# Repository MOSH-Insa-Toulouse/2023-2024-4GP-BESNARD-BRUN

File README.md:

# 2023-2024 : Capteur low-tech Graphite (Niels Brun &amp; Paul Besnard)

## SOMMAIRE
*** 
  - [Contexte](#contexte)
  - [Livrables](#livrables)
  - [Matériel nécessaire](#matériel-nécessaire)
  - [1. Simulation électronique du capteur sous LTSpice](#simulation-électronique-du-capteur-sous-ltspice)
  - [2. Design du PCB sous KiCad](#design-du-pcb-sous-kicad)
  - [3. Code arduino](#code-arduino)
  - [4. Application android APK sous MIT App Inventor](#application-android-apk-sous-mit-app-inventor)
  - [5. Réalisation du shield](#réalisation-du-shield)
  - [6. Banc de test](#banc-de-test)
  - [7. Datasheet](#datasheet)
  - [Contact](#contact) 

*** 

## Contexte
&nbsp;&nbsp;&nbsp;&nbsp;&nbsp;&nbsp;Dans le cadre de l'UF "Du capteur au banc de test" se déroulant en 4ème année de Génie Physique de l’INSA Toulouse, nous avons développé un dispositif permettant de mesurer la contrainte. Le capteur du dispositif est basé sur l'article "Pencil Drawn Strain Gauges and Chemiresistors on Paper" (Cheng-Wei Lin*, Zhibo Zhao*, Jaemyung Kim & Jiaxing Huang). Il est simplement composé d'un bout de papier avec du graphite que l'on vient déposer à l'aide d'un crayon à papier. En déformant le papier, le nombre de particules de graphite reliées, composant le crayon à papier déposé sur le papier, varie en fonction du type de déformation. Ce système granulaire subit une modification de résistance et de conductance. Grâce à cela, on  pourra remonter à la déformation tel une jauge de contrainte traditionnel. \
&nbsp;&nbsp;&nbsp;&nbsp;&nbsp;&nbsp;L'objectif est donc de pouvoir réaliser un dispositif permettant la mesure de déformation à partir d'un capteur low-tech. En passant par différentes étapes : simulations électroniques, design du PCB, code arduino et réalisation de datasheet.

## Livrables
- Un Shield PCB relié à une carte arduino UNO avec différents composants : un capteur graphite, un amplificateur transimpédance et un module bluetooth. Il peut également avoir un écran OLED, un flex sensor commercial, un potentiomètre digital, encodeur rotatoire ou des boutons.
- Un code arduino qui gère les différents composants cités précédemments (mesures de contraintes, échanges bluetooth et OLED, potentiomètre digital et boutons)
- Une application Android (sous MIT App Inventor) interfaçant le PCB et le code arduino.
- Un code arduino réalisant les essais de banc de test sur les mesures de contraintes.
- Une datasheet sur le capteur de contrainte.

&nbsp;&nbsp;&nbsp;&nbsp;&nbsp;&nbsp;Nous avons opté pour l'ajout d'un écran OLED, du flex sensor commercial, du potentiomètre digital. Egalement, nous avons choisi l'implémentation de 3 boutons plutôt que de l'encodeur rotatoire.

## Matériel nécessaire
Pour réaliser notre dispositif électronique, voici la liste des composants nécessaires :

- Résistances : 1 de 1 $k\ohm$, 1 de $10k\ohm$, 2 de $100k\ohm$ pour l'amplificateur transimpédance. 3 de $10k\ohm$ pour les boutons (peuvent être éviter en utilisant les résistances internes de l'arduino) et 1 de $47k\ohm$ pour le flex sensor.
- Capacités : 3 de 100 nF, 1 de 1 uF
- Arduino Uno
- Amplificateur opérationnel LTC1050
- Potentiomètre digital MCP41050
- Module Bluetooth HC05
- Ecran OLED 128x64
- Flex Sensor
- 3 boutons

## Simulation électronique du capteur sous LTSpice
&nbsp;&nbsp;&nbsp;&nbsp;&nbsp;&nbsp;Notre capteur de graphite possède une résistance variable de l'ordre du gigaohm. Le courant alors généré lorsque l'on applique une tension de 5V aux bornes du capteur est très faible (de l'ordre de la dizaine de nanoampères). Ainsi, pour récupérer et pouvoir analyser ce signal, nous devons l'amplifier. C'est pourquoi nous avons utilisé un montage transimpédance constitué d'un amplificateur opérationnel (AOP) pour fournir un signal en tension suffisant au convertisseur analogique-numérique (ADC) d'une carte Arduino UNO. \
Nous avons testé ce montage sur le logiciel LTspice basé sur [ce schéma](https://github.com/MOSH-Insa-Toulouse/2023-2024-4GP-BESNARD-BRUN/blob/main/Images/LTspice/schema_suggere.png) . Voici son schéma :

&nbsp;&nbsp;&nbsp;&nbsp;&nbsp;&nbsp;Concernant le choix de notre AOP, celui-ci devait être capable d'accepter en entrée un très faible courant. Il doit également avoir un offset de tension très faible afin de ne pas fausser les valeurs de tension transmises à l'ADC qui seront ensuite analysées. C'est pourquoi nous avons choisi le LTC 1050.
A ce circuit amplificateur, nous avons ajouté trois filtres pour notre signal :

- à l'entrée, un filtre passe-bas passif (R1,C1) de fréquence de coupure de 16 Hz. Il permet de filtrer les bruits en courant sur le signal d'entrée
- un autre filtre passe bas de fréquence de coupure de 1.6 Hz (R3,C4) couplé à l'AOP. Ce filtre actif permet de filtrer la composante du bruit à 50 Hz provenant du réseau électrique
- à la sortie de l'amplificateur, un dernier filtre (R6,C2) de 1.6 kHz permet de retirer le bruit créé en cours de traitement (bruits des alimentation, de l'horloge etc...)

&nbsp;&nbsp;&nbsp;&nbsp;&nbsp;&nbsp;Egalement, nous avons placé la capacité C3 de sorte à ce qu'elle filtre le bruit de l'alimentation. Aussi, la résistance R5 en entrée protège l'AOP contre les décharges électrostatiques en plus de formé avec la capacité C1 un filtre pour les bruits en tension. Enfin, la résistance R2 sera remplacé plus tard par un potentiomètre digital. Cela nous permettra de régler le gain de notre AOP en fonction de nos besoins.

Nous avons donc testé notre circuit afin de savoir si nos filtres seraient efficients :

Voici la réponse de notre circuit pour vérfier que le capteur soit correctement amplifié : 

Le signal est amplifié à 1V donc l'arduino UNO pourra le mesurer.

Enfin, voici la réponse lorsque l'on simule un courant alternatif pour vérifier que le bruit est bien filtré.

On remarque que le bruit est bien atténué, à 50Hz, il est atténue d'environ 72 dB.

## Design du PCB sous KiCad

&nbsp;&nbsp;&nbsp;&nbsp;&nbsp;&nbsp;Afin de réaliser notre PCB, nous avons reproduit le circuit précédent sur Kicad 7.0. 
Nous avons remplacé la résistance R2 par un potentiomètre numérique afin de pouvoir faire varier le gain de notre AOP. Egalement, nous avons rajouté divers composants afin de pouvoir mesurer efficacement notre capteur graphite et comparé les résultats obtenus :
- un flexsensor servant de témoin, afin de pouvoir comparer nos mesures avec celle du capteur en graphite
- un module bluetooth HC-05 afin de pouvoir communiquer avec notre circuit depuis notre téléphone depuis une application mobile que nous coderons nous-même. 
- un écran OLED ainsi que trois boutons poussoirs afin de pouvoir visualiser le résultats de nos mesures et pouvoir naviguer simplement dans les différents menus permettant diverses mesures

&nbsp;&nbsp;&nbsp;&nbsp;&nbsp;&nbsp;Tous nos composants seront installés sur un shield d'Arduino UNO. 

&nbsp;&nbsp;&nbsp;&nbsp;&nbsp;&nbsp;Nous avons commencé par réaliser les symboles des différents composants et reproduire le schéma électrique complet sur Kicad. Voici le schéma électrique de l'ensemble de notre montage :

&nbsp;&nbsp;&nbsp;&nbsp;&nbsp;&nbsp;Nous avons par la suite réalisé les empreintes de nos composants afin de les placer sur notre PCB. Notre difficulté principale a été de placer les composants de sorte qu'il n'y ait pas de via, notamment pour le GND. Voici le résultat final :

&nbsp;&nbsp;&nbsp;&nbsp;&nbsp;&nbsp;Et voici le rendu 3D que nous obtenu avec ces routages : 

&nbsp;&nbsp;&nbsp;&nbsp;&nbsp;&nbsp;Toutes les ressources utilisées pour notre Kicad (empreintes, schéma etc...) sont disponibles dans notre [dossier Kicad](https://github.com/MOSH-Insa-Toulouse/2023-2024-4GP-BESNARD-BRUN/tree/main/Kicad).

## Code arduino
&nbsp;&nbsp;&nbsp;&nbsp;&nbsp;&nbsp;Nous avons utilisé l'IDE Arduino 2.3.2. Nous avons utilisé les librairies SoftwareSerial pour le bluetooth et Adafruit_SSD1306 pour l'écran OLED. Sur cette dernière, elle utilise beaucoup de RAM pour les buffers, cette utilisation de RAM n'est pas affiché par l'IDE Arduino. Il se peut que le programme ne se lance pas si une attention n'a pas été porté sur cette utilisation de RAM. Pour éviter cela, on peut utiliser  la fonction ["F()"](https://www.arduino.cc/reference/en/language/variables/utilities/progmem/), utiliser des librairies pour l'écran OLED moins gourmandes ou enfin diminuer la résolution de l'écran.

&nbsp;&nbsp;&nbsp;&nbsp;&nbsp;&nbsp;Dans le [dossier arduino](https://github.com/MOSH-Insa-Toulouse/2023-2024-4GP-BESNARD-BRUN/tree/main/Arduino) se trouve les différents fichiers pour tester les multiples éléments du dispositif. \
Concernant le [fichier principal](https://github.com/MOSH-Insa-Toulouse/2023-2024-4GP-BESNARD-BRUN/blob/main/Arduino/Main/Main.ino) : lors de la mise sous tension de l'arduino, une première calibration du potentiomètre digitale est faite en fonction de la valeur mesurée sur le capteur graphite. 
Suite à cela, le dispositif est par défaut dans le menu déroulant avec 4 choix : 
- une mesure instantannée toutes les 500 ms
- une mesure moyennée sur 2500 ms
- une mesure du flex sensor commercial et enfin 
- une calibration du potentiomètre digital

&nbsp;&nbsp;&nbsp;&nbsp;&nbsp;&nbsp;Le choix de menu se fait grâce aux 3 boutons : un pour descendre dans le menu, un pour monter dans le menu et un troisième pour valider le choix. Ce dernier bouton de validation sert également à sortir du menu choisi.

&nbsp;&nbsp;&nbsp;&nbsp;&nbsp;&nbsp;Chaque choix du menu appel une fonction différente qui réalise sa mesure et qui est envoyé à la fonction DisplayAndTransmitter afin de l'afficher sur l'écran OLED et l'envoyer sur l'application bluetooth. Tant que le bouton central de "validation" n'est pas appuyé, on reste dans cette boucle de mesure et d'affichage.

&nbsp;&nbsp;&nbsp;&nbsp;&nbsp;&nbsp;Le calcul de la résistance du capteur en graphite se fait avec : $$Res=R1*(1+\frac{R3}{R2})*\frac{Vcc}{Vadc}-R1-R5$$ \
&nbsp;&nbsp;&nbsp;&nbsp;&nbsp;&nbsp;Et dans notre cas, notre résistance R2 est variable : c'est celle du potentiomètre digital qui est calculé avec : $`R2=\frac{47500*pos}{256}+125`$ où notre $47500$ correspond à la valeur de résistance maximale de notre MCP41050 et $pos$ la position du potentiomètre parmi les 256 valeurs.

## Application android APK sous MIT App Inventor
&nbsp;&nbsp;&nbsp;&nbsp;&nbsp;&nbsp;Une application est également disponible avec le dispositif : développé sous [MIT App Inventor](https://appinventor.mit.edu/) . 

&nbsp;&nbsp;&nbsp;&nbsp;&nbsp;&nbsp;L'application reçoit les données transmis par le module bluetooth HC-05. Elle affiche ensuite la valeur tranmis (des $M\ohm$ pour le capteur graphite ou des $\ohm$ pour le flex sensor.

&nbsp;&nbsp;&nbsp;&nbsp;&nbsp;&nbsp;L'application peut s'installer [sous android ici](https://github.com/MOSH-Insa-Toulouse/2023-2024-4GP-BESNARD-BRUN/tree/main/Android/CapteurGraphite.apk) et toutes les informations liées à l'application son dans [le dossier Application Android](https://github.com/MOSH-Insa-Toulouse/2023-2024-4GP-BESNARD-BRUN/tree/main/Android)

## Réalisation du shield

&nbsp;&nbsp;&nbsp;&nbsp;&nbsp;&nbsp;Grâce à notre Kicad, nous avons pu éditer un masque de gravure de notre PCB. Nous avons envoyé notre projet Kicad à Cathy qui s'est chargée de l'imprimer. Elle a ensuite insolé aux UV une plaque d'Epoxy recouverte d'une fine couche de cuivre et d'une résine photosensible. Puis, elle a plongé la plaquette insolée dans du révélateur afin de retirer la résine non insolée, puis dans du perchlorure de fer afin de graver les pistes. Enfin, elle a nettoyé notre plaquette avec de l'acétone afin de retirer la résine restante. Merci beaucoup à Cathy qui a pris le temps de tirer notre PCB et nous expliquer le processus de fabrication!

&nbsp;&nbsp;&nbsp;&nbsp;&nbsp;&nbsp;Nous avons ensuite procéder au perçage de notre plaquette afin de pouvoir installer nos différents composants selon le schéma du PCB obtenu grâce à Kicad. Une fois le perçage terminé, nous avons soudé nos composants à la plaquette.

&nbsp;&nbsp;&nbsp;&nbsp;&nbsp;&nbsp;Lors de cette étape, l'installation de nos composants a été plus compliquée que prévue. En effet, l'ensemble de nos trous étaient légèrement décalés par rapport à leur emplacement prévu. L'origine de ce problème n'a pas été clairement établie.

## Banc de test

&nbsp;&nbsp;&nbsp;&nbsp;&nbsp;&nbsp;Pour spécifier notre capteur et son montage transimpédance, nous avons décidé d'utiliser des demis-cercles avec un rayon différents.

&nbsp;&nbsp;&nbsp;&nbsp;&nbsp;&nbsp;Ce sont des demis-cercles, imprimés en 3D, avec un diamètre commençant à 2 cm pour le plus petit et en augmentant de 0.5 cm par créneau. Le plus grand demi-cercle a un diamètre de 5cm. Grâce à ces demis-cercles, nous allons pouvoir calculer la variation de la résistance électrique $\frac{\Delta R}{R_0}$ en fonction de la déformation $\epsilon=\frac{e}{D}$. Nous avons ici mesuré notre épaisseur de notre papier $e=0.2 mm$. Ainsi, nous avons une déformation variant de 0.1 pour le plus petit diamètre à 0.04 pour le plus grand. Voici les courbes caractéristiques pour des crayons 2B, B et HB pour [des tensions ou des compressions.](https://github.com/MOSH-Insa-Toulouse/2023-2024-4GP-BESNARD-BRUN/tree/main/Images/Compression-Tension.png)

&nbsp;&nbsp;&nbsp;&nbsp;&nbsp;&nbsp;On remarque que la résistance augmente lorsque l'on met le capteur en tension et qu'elle diminue lors de la compression de ce dernier. En tension, la distance entre les atomes de carbones augmente et la résistance augmente avec. Le contraire se produit pour la compression. \
&nbsp;&nbsp;&nbsp;&nbsp;&nbsp;&nbsp;En fonction de la dureté du crayon utilisé, les variations relatives de résistance changent. Plus le crayon est gras (2H->H->HB->B->2B avec 2B avec le plus de carbone), moins sa variation relative de résistance est élevée.

&nbsp;&nbsp;&nbsp;&nbsp;&nbsp;&nbsp;De plus, contrairement, à l'article "Pencil Drawn Strain Gauges and Chemiresistors on Paper" (Cheng-Wei Lin*, Zhibo Zhao*, Jaemyung Kim & Jiaxing Huang), nous avons pu mesurer la résistance avec un crayon 2H.

&nbsp;&nbsp;&nbsp;&nbsp;&nbsp;&nbsp;Enfin, on peut comparer notre capteur avec un flex sensor commercial. Il semblerait que le flex sensor soit plus sensible à la déformation, en plus d'être plus solide pour des déformations importantes. Pour notre capteur, il a un nombre d'utilisation très limité, qui diminue très fortement pour une déformation élevée.

&nbsp;&nbsp;&nbsp;&nbsp;&nbsp;&nbsp;Néanmoins, toutes ces mesures sont à prendre avec du recul au vu des conditions non reproductibles d'essai. En effet, la quantité de graphite déposée au crayon à papier est très variable, induisant ainsi une résistance très variable. Il serait intéressant de développer une méthode afin de déposer une quantité fixe et reproductible de graphite.
&nbsp;&nbsp;&nbsp;&nbsp;&nbsp;&nbsp;Egalement, nous conseillerons de changer de banc de test et d'utiliser un servo-moteur qui permet de créer des conditions plus reproductibles, que ce soit pour le carbone qui n'est pas déposé sur le banc de test mais également par l'angle imposé qui est précisement connu. Autrement, il faudrait reproduire des cercles de diamètres connues mais avec des déformations moins importantes afin de moins endommager le capteur.

## Datasheet

&nbsp;&nbsp;&nbsp;&nbsp;&nbsp;&nbsp; Vous pouvez retrouver la datasheet du produit [ici](https://github.com/MOSH-Insa-Toulouse/2023-2024-4GP-BESNARD-BRUN/tree/main/datasheet.pdf)

## Contact

&nbsp;&nbsp;&nbsp;&nbsp;&nbsp;&nbsp;Vous pouvez nous contacter pour toutes questions :
- Niels Brun : niels.brun@insa-toulouse.fr
- Paul Besnard : paul.besnard@insa-toulouse.fr

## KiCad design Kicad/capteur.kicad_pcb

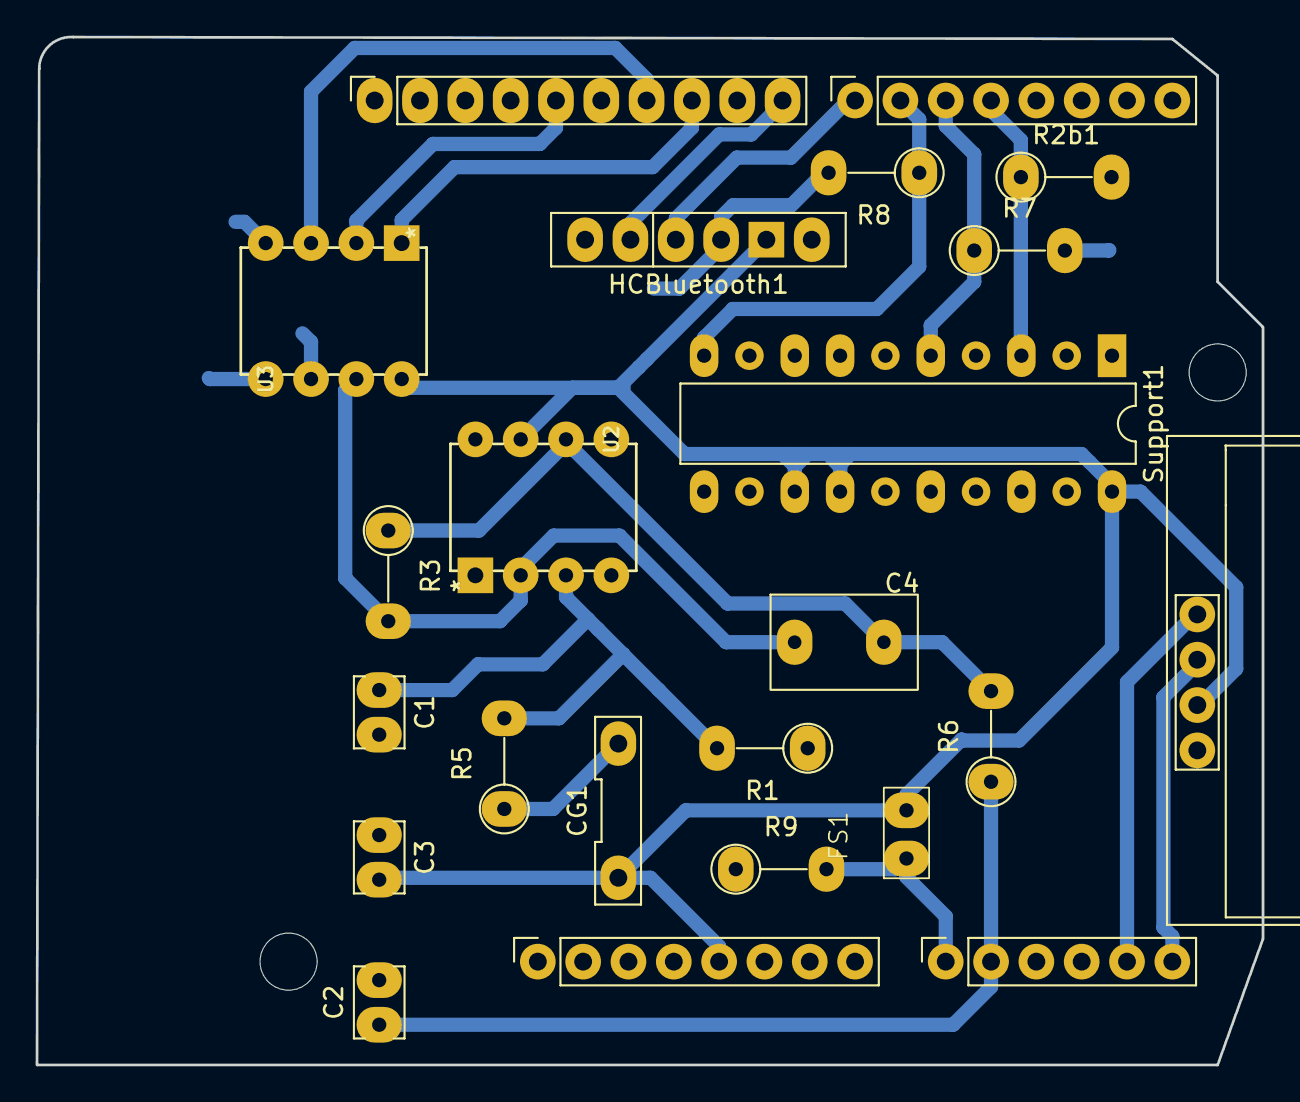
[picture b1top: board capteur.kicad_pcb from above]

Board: 2 copper layers, 68.7 x 57.6 mm, 25 parts (0 on the bottom side), 18 nets.

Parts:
Brd1: SSD1306; 128x64OLED
C1, C2, C3: C; capa
C4: C; C4
CG1: CG
FS1: FlexSensor
HCBluetooth1: Bluetooth_HC-05
J1: Power; PinSocket_1x08_P2.54mm_Vertical
J2: Digital/PWM; PinSocket_1x10_P2.54mm_Vertical
J3: Analog; PinSocket_1x06_P2.54mm_Vertical
J4: Digital/PWM; PinSocket_1x08_P2.54mm_Vertical
MH2, MH3: MountingHole_3.2mm
R1, R2b1, R3, R5, R6, R7, R8, R9: R; R_Axial_DIN0207_L6.3mm_D2.5mm_P5.08mm_Vertical
Support1: DIP-20_W7.62mm_LongPads
U2: LTC1050ACN8; LTC
U3: MCP41100; LTC

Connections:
+5V: Brd1.2 (VCC), C3.2, CG1.1 (Vcc), FS1.2 (Vcc), HCBluetooth1.4 (Vcc), J1.5, Support1.1 (Vcc), Support1.4 (Vcc), Support1.5 (Vcc), U2.7 (V+), U3.8 (VDD)
/4: J4.4, R2b1.1, Support1.2 (Out)
/7: HCBluetooth1.2 (TX), J4.1
/8: HCBluetooth1.1 (RX), J2.10
/13: J2.5, U3.2 (SCK)
/*5: J4.3, R7.1, Support1.3 (Out)
/*6: J4.2, R8.1, Support1.6 (Out)
/*10: J2.8, U3.1 (~CS)
/*11: J2.7, U3.3 (SI)
/A0: FS1.1 (Vout), J3.1, R9.2
/A1: C2.1, J3.2, R6.1
/R2: C4.1, R3.2, U2.2 (-IN), U3.7 (PB0)
/SCL/A5: Brd1.3 (SCL), J2.1, J3.6
/SDA/A4: Brd1.4 (SDA), J2.2, J3.5
GND: Brd1.1 (GND), C1.2, C2.2, C3.1, HCBluetooth1.3 (GND), J1.6, J1.7, J2.4, R1.1, R2b1.2, R7.2, R8.2, R9.1, U2.4 (V-), U3.4 (VSS), U3.5 (PA0), U3.6 (PW0)
unnamed: CG1.2 (Vout), R5.1
unnamed: C1.1, R1.2, R5.2, U2.3 (+IN)
unnamed: C4.2, R3.1, R6.2, U2.6 (OUT)

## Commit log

2024-03-23 Update README.md adding a part of the LTspice part
2024-03-25 update of readme
2024-03-26 small change of pcb and update of readme
2024-03-27 add of image and minor change for main.ino
2024-03-27 Update README.md
    Kicad + réalisation du shield written!
2024-04-01 minor change
2024-04-03 Add of images and update of readme
2024-04-12 syntax changes of readme
2024-04-19 Update README.md
    Correction mineure d'erreurs de syntaxe
2024-04-24 add of datasheet, remake of test bench and add of readme
2024-05-07 Rename Datasheeet.pdf to Datasheet.pdf
2024-05-07 Rename Datasheet.pdf to datasheet.pdf

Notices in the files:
parts and their libraries:
COPYRIGHT: Copyright C 2016 Accelerated Designs. All rights reserved
